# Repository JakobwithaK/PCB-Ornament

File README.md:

# PCB-Ornament
Custom designed PCB ornament using the Attiny85

# Improvements/Things I Learned For Next Time.
* Add pin header for power and ground to remove need to solder them when programming. 
* Can use a serial in parallel out shift register to free up pins on the Attiny85 and also use a matrix to drive more LEDs
* Look into more power saving options, for example: disable ADC and reduce clock frequency

# Pictures:

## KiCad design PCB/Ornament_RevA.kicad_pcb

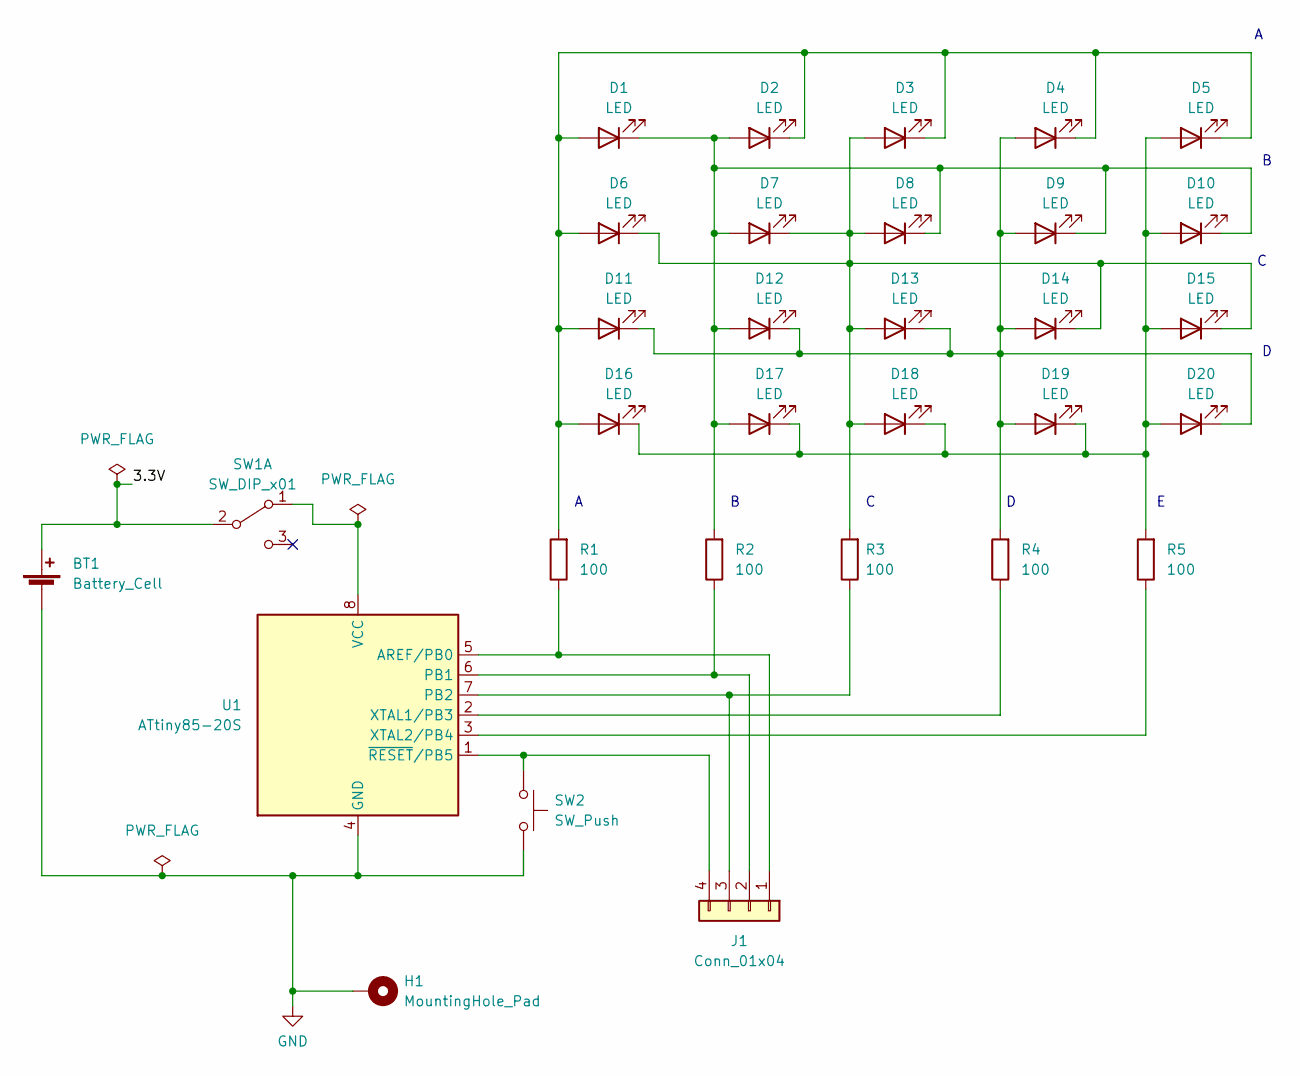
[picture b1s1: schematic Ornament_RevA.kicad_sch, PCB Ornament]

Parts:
BT1: Battery_Cell; BatteryHolder_Keystone_1058_1x2032
D1, D2, D3, D4, D5, D6, D7, D8, D9, D10, D11, D12, D13, D14, D15, D16, D17, D18, D19, D20: LED; D_1206_3216Metric_Pad1.42x1.75mm_HandSolder
H1: MountingHole_Pad; MountingHole_2.7mm_Pad
J1: Conn_01x04; PinSocket_1x04_P2.54mm_Vertical
R1, R2, R3, R4, R5: 100; R_1206_3216Metric_Pad1.30x1.75mm_HandSolder
SW1: SW_DIP_x01; JS102011SCQN__Switch
SW2: SW_Push; TL3305AF160QG_Push_Button
U1: ATtiny85-20S; SOIC-8W_5.3x5.3mm_P1.27mm

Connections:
/3.3V: BT1.1 (+), SW1.2 (B)
GND: BT1.2 (-), H1.1, SW2.2, U1.4 (GND)
unnamed: D1.1 (K), D2.2 (A), D7.2 (A), D8.1 (K), D9.1 (K), D10.1 (K), D12.2 (A), D17.2 (A), R2.2
unnamed: D1.2 (A), D2.1 (K), D3.1 (K), D4.1 (K), D5.1 (K), D6.2 (A), D11.2 (A), D16.2 (A), R1.2
unnamed: D5.2 (A), D10.2 (A), D15.2 (A), D16.1 (K), D17.1 (K), D18.1 (K), D19.1 (K), D20.2 (A), R5.2
unnamed: D4.2 (A), D9.2 (A), D11.1 (K), D12.1 (K), D13.1 (K), D14.2 (A), D19.2 (A), D20.1 (K), R4.2
unnamed: D3.2 (A), D6.1 (K), D7.1 (K), D8.2 (A), D13.2 (A), D14.1 (K), D15.1 (K), D18.2 (A), R3.2
unnamed: J1.1, R1.1, U1.5 (AREF/PB0)
unnamed: J1.2, R2.1, U1.6 (PB1)
unnamed: J1.3, R3.1, U1.7 (PB2)
unnamed: J1.4, SW2.1, U1.1 (~RESET/PB5)
unnamed: R4.1, U1.2 (XTAL1/PB3)
unnamed: R5.1, U1.3 (XTAL2/PB4)
unnamed: SW1.1 (A), U1.8 (VCC)

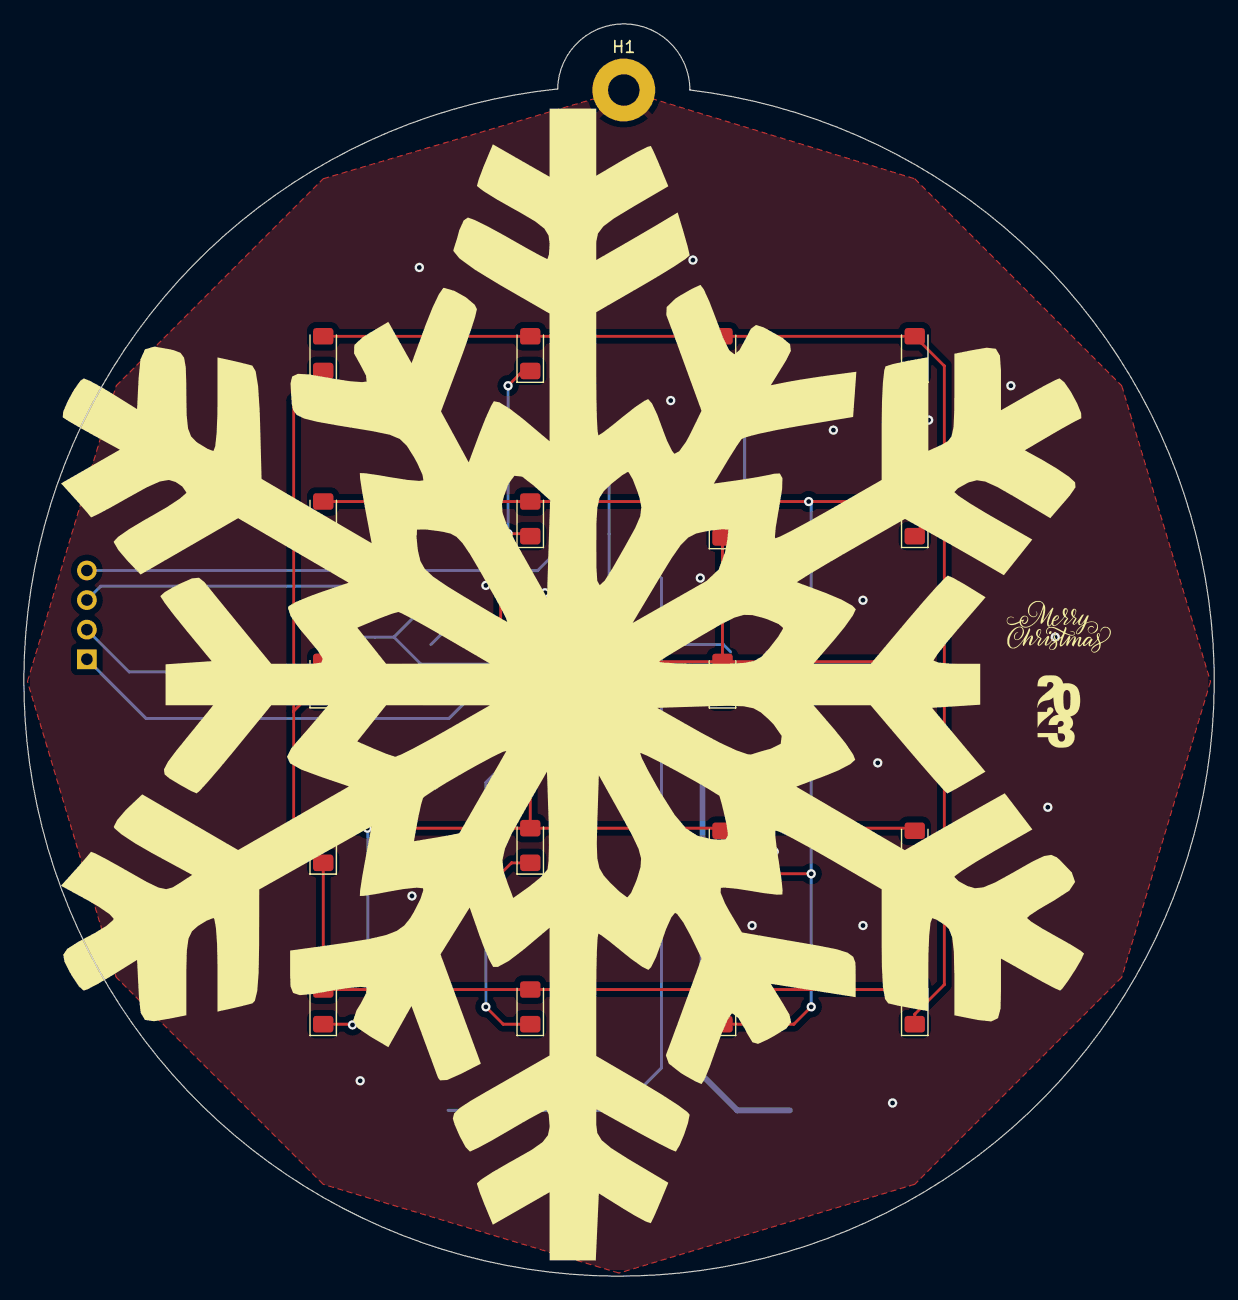
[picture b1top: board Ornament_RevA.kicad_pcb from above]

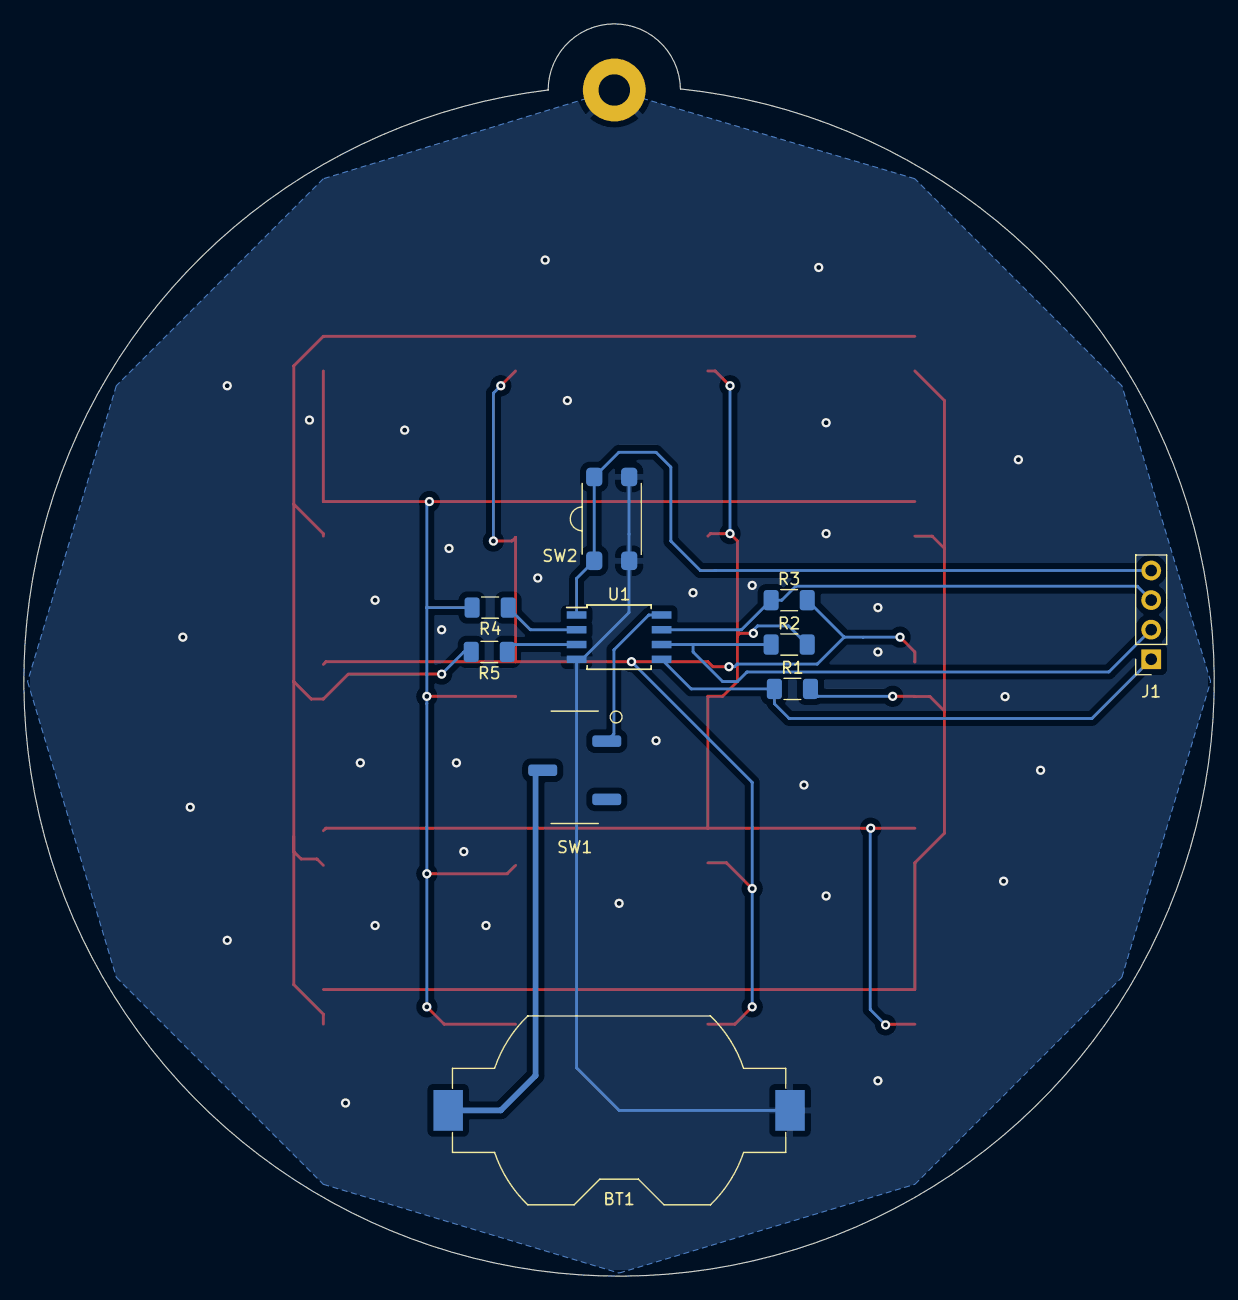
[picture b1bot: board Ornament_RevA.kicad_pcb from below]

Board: 2 copper layers, 102.2 x 107.5 mm, 31 parts (10 on the bottom side), 14 nets.

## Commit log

2023-12-15 adding Ornament V1.0
